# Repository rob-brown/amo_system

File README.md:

# AMO System

The Amiibo Modular Open System (AMO System) includes several components for working
with and automating amiibo on Nintendo Switch. This includes emulating a bluetooth
controller, computer vision, reading/writing amiibo files, and more. See the README
files in the respective packages in the [`apps`](apps) directory for more details about each.

# Support Us

If you want to support the development, you can [donate to the cause](https://donate.stripe.com/28ocQi4Ur9TNclW000).

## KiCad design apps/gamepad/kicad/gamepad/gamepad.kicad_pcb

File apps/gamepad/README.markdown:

# Gamepad

## Summary

The Gamepad code is able to emulate a Nintendo Switch Pro Controller. It
serves up a web interface on your local network to support loading amiibo.

## Demo

With the gamepad, you can store all your amiibo in one place. Even with large
collections of amiibo you can organize them with tags. You can pull up any of
your trained amiibo and load them into Super Smash Bros. Ultimate. With the
shuffle button, you can even load the same amiibo multiple times.

You can also use it in other games such as Tears of the Kingdom. With the
shuffle function, you can load the same amiibo repeatedly, making this the
fastest way to farm items. Note, this only works with the proxy gamepad option
since you need a joystick and L button.

Item farming is also useful in other games such as Hyrule Warriors and Skyrim.
However, Hyrule Warriors limits the number of scans per day (5). Skyrim limits
one scan per day for each amiibo ID (not serial number). You will still need to
wait or change the system clock to scan more amiibo. Other games may have similar
restrictions.

## Search

Within an amiibo collection, you can search your amiibo based on name, character,
id, and tags. Any SSBU amiibo can be search by character, ex. `character:zelda`.
You can also create any tags you want and apply them to your amiibo. You can search
tags like this: `tag:tears_of_the_kindgom`. Note that spaces in tag names must
be replaced with underscores (`_`). IDs can be searched using base16 encoding.
Partial IDs can be searched by the first bytes. For example, the full ID
`id:01070000035a0902` is not necessary. Searching `id:01070000` or `id:0107` is
often sufficient. Names can be searched without any prefix, ex. `billy`. All search
terms are case insenstive.

## Assembly

This repo includes three hardware options.

1. A simple option based on the [Adafruit Joy Bonnet](./docs/joybonnet.markdown).

2. The [AmmoBox](./docs/ammobox.markdown), a built-from-scratch option including a
custom circuit board.

3. A bring-your-own-hardware option. You plug a USB gamepad into the Pi and the
buttons and sticks are [proxied](apps/proxy_gamepad) to the Nintendo Switch via bluetooth.

Alternatively, you can make your own hardware and adjust the code accordingly.

## Initial Setup

See the common [OS Setup doc](../../docs/os-setup.markdown) for details to
install an OS for the Raspberry Pi.

## Joycontrol Installation

First, you will need to install
[Joycontrol and its dependencies](https://github.com/poohl/joycontrol).
This involves editing some system files too. You will need to manually run the
`run_controller_cli.py` script to pair your Nintendo Switch to your Raspberry Pi.

**When running joycontrol, note the MAC address if connecting to a Nintendo Switch 2**

## Gamepad Installation

You probably have `curl` and `cron` already installed. If you don't have them
installed, then you can do so like this:

```bash
sudo apt update
sudo apt install curl cron --yes
```

You can install the app for AmmoBox like this:

```bash
curl -fsSL https://raw.githubusercontent.com/rob-brown/amo_system/main/apps/gamepad/apps/hardware/install.sh | bash -s -- ammobox
```

For the Joy Bonnet:

```bash
curl -fsSL https://raw.githubusercontent.com/rob-brown/amo_system/main/apps/gamepad/apps/hardware/install.sh | bash -s -- joybonnet
```

The only difference is the platform name at the end.

If you instead want the proxy gamepad, run this for a Nintendo Switch:

```bash
curl -fsSL https://raw.githubusercontent.com/rob-brown/amo_system/main/apps/gamepad/apps/proxy_gamepad/install.sh | bash
```

If using a Nintendo Switch 2, run the following, replacing `01:23:45:67:89:AB` with the
MAC address you found when manually running Joycontrol earlier.

```bash
curl -fsSL https://raw.githubusercontent.com/rob-brown/amo_system/main/apps/gamepad/apps/proxy_gamepad/install.sh | bash -s -- 01:23:45:67:89:AB
```

> **WARNING:** You shouldn't just trust someone to run an arbitrary script on your
system, especially one that has root permissions like this one does. Take some
time and look over the script to ensure it's not doing anything nefarious. You
can also run the commands yourself to better see the effects.

Once you've installed the app, you will need to pair your Pi with your Nintendo
Switch. Then every time after your Pi boots, it will try to connect to your
Nintendo Switch.

## Web Interface

See the [web interface doc](./docs/web-interface.markdown) for details on how to use
the web interface to load and use amiibo.

## Troubleshooting

If you are having trouble with the web interface, make sure your cron file (ex. `/etc/cron.d/proxy`) is using the same
host name as your Pi. You can find the host name by running `hostname` from the console. If your host name is `raspberrypi`,
then make sure your cron file has `PHX_HOST=raspberrypi.local`.

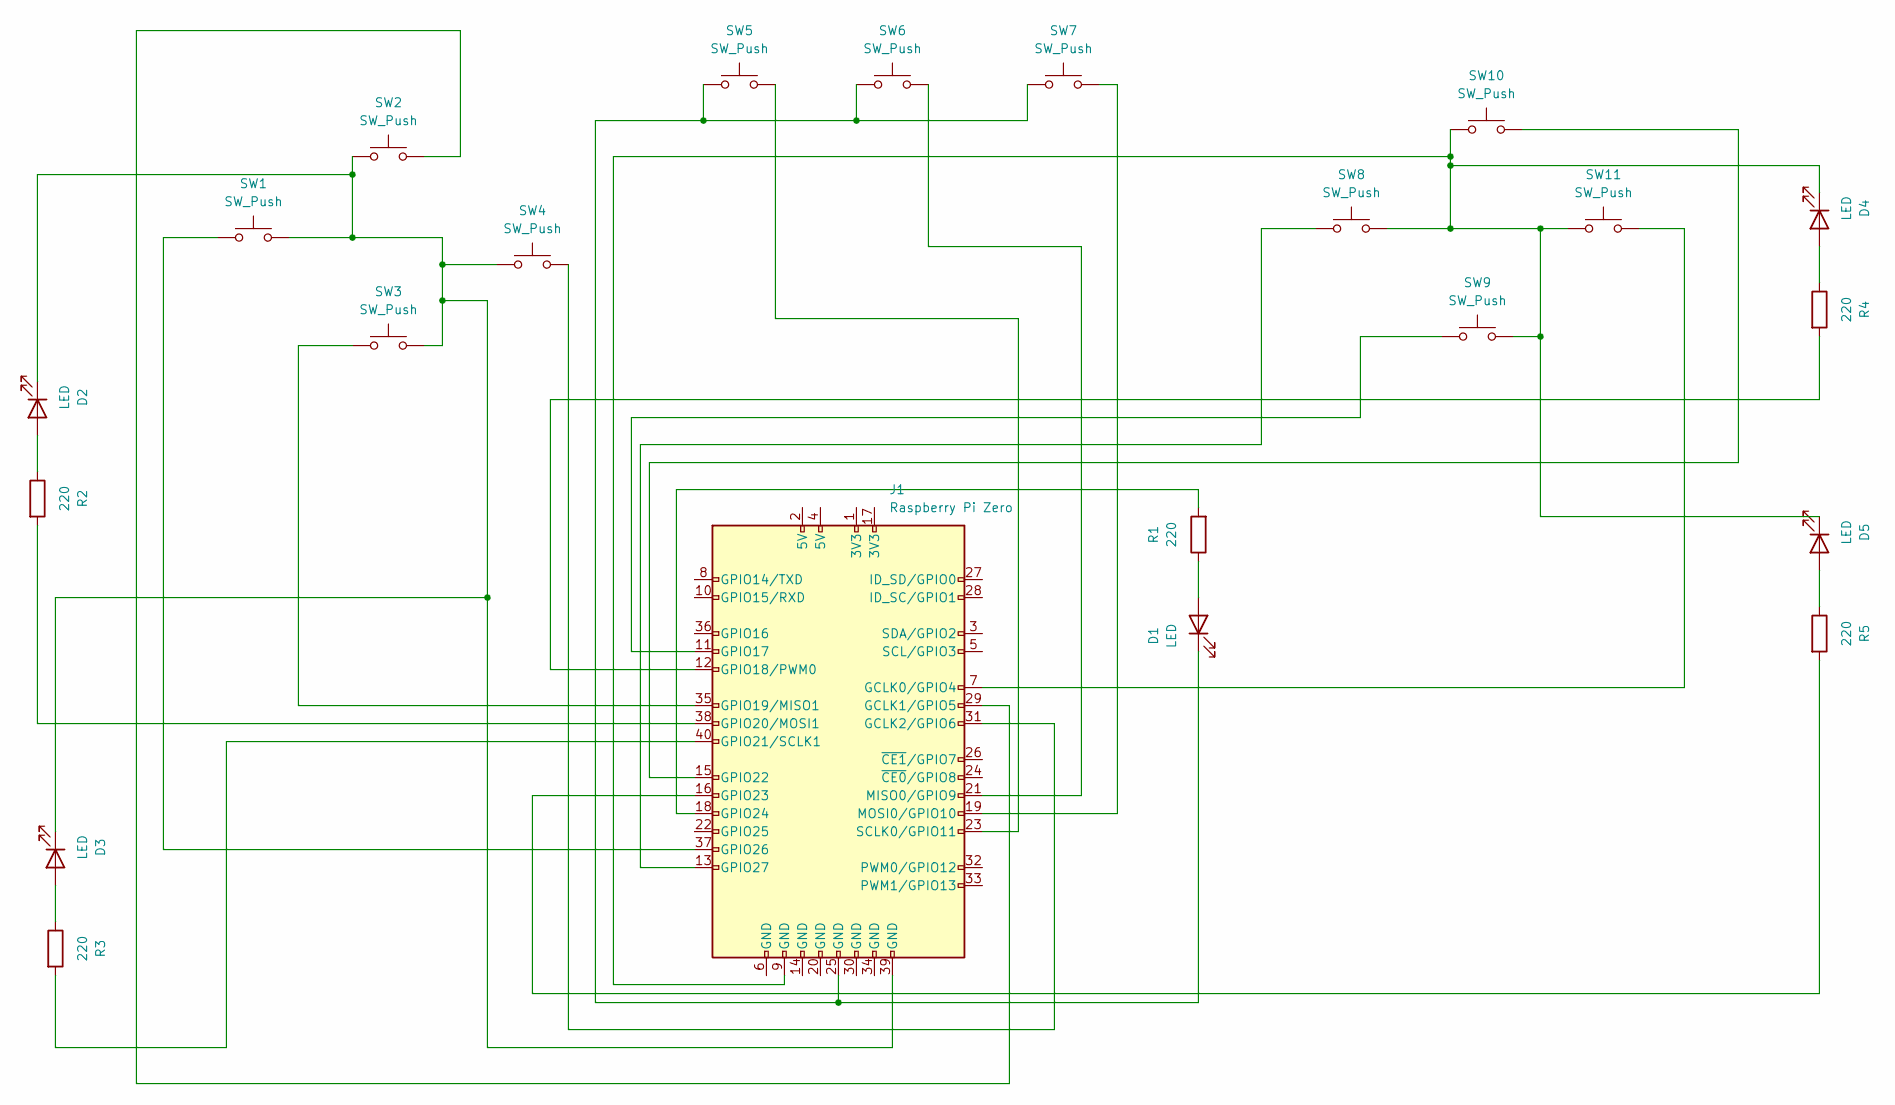
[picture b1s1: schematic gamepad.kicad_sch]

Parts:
D1: LED; LED_D3.0mm_Horizontal_O1.27mm_Z2.0mm
D2, D3, D4, D5: LED; LED_D5.0mm
J1: Raspberry Pi Zero; PinHeader_2x20_P2.54mm_Vertical
R1, R2, R3, R4, R5: 220; R_Axial_DIN0204_L3.6mm_D1.6mm_P7.62mm_Horizontal
SW1, SW2, SW3, SW4, SW5, SW6, SW7, SW8, SW9, SW10, SW11: SW_Push; SW_PUSH_6mm_H5mm

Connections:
unnamed: D1.1 (K), J1.25 (GND), SW5.1, SW6.1, SW7.1
unnamed: D1.2 (A), R1.1
unnamed: D2.2 (A), R2.1
unnamed: D3.2 (A), R3.1
unnamed: D4.2 (A), R4.1
unnamed: D5.2 (A), R5.1
unnamed: J1.7 (GCLK0/GPIO4), SW11.2
unnamed: D4.1 (K), D5.1 (K), J1.9 (GND), SW8.2, SW9.2, SW10.1, SW11.1
unnamed: J1.11 (GPIO17), SW9.1
unnamed: J1.12 (GPIO18/PWM0), R4.2
unnamed: J1.13 (GPIO27), SW8.1
unnamed: J1.15 (GPIO22), SW10.2
unnamed: J1.16 (GPIO23), R5.2
unnamed: J1.18 (GPIO24), R1.2
unnamed: J1.19 (MOSI0/GPIO10), SW7.2
unnamed: J1.21 (MISO0/GPIO9), SW6.2
unnamed: J1.23 (SCLK0/GPIO11), SW5.2
unnamed: J1.29 (GCLK1/GPIO5), SW2.2
unnamed: J1.31 (GCLK2/GPIO6), SW4.2
unnamed: J1.35 (GPIO19/MISO1), SW3.1
unnamed: J1.37 (GPIO26), SW1.1
unnamed: J1.38 (GPIO20/MOSI1), R2.2
unnamed: D2.1 (K), D3.1 (K), J1.39 (GND), SW1.2, SW2.1, SW3.2, SW4.1
unnamed: J1.40 (GPIO21/SCLK1), R3.2

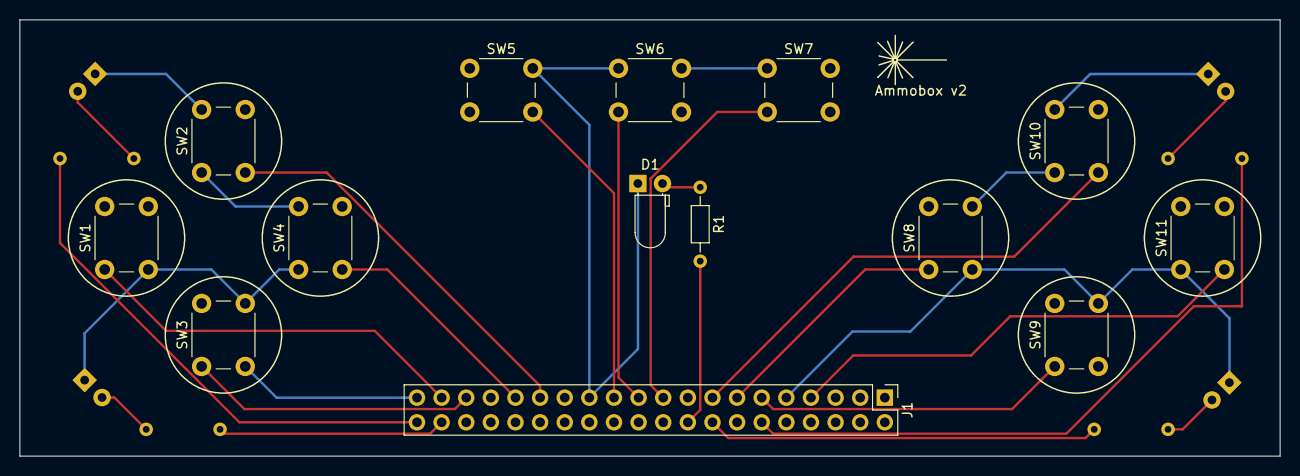
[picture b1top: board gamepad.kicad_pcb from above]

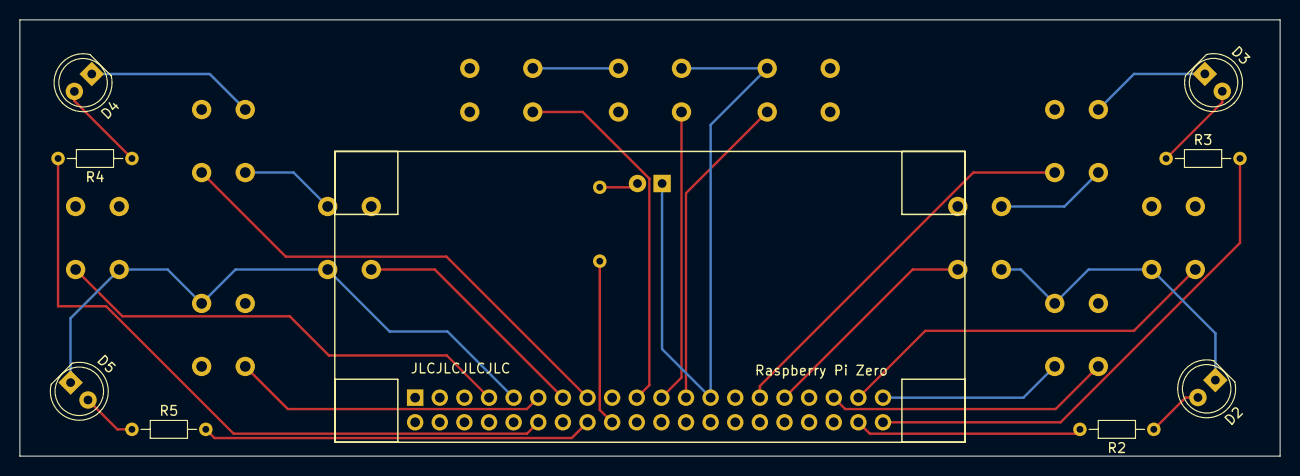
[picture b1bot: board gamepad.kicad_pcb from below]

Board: 2 copper layers, 130.0 x 45.0 mm, 22 parts (8 on the bottom side), 24 nets.

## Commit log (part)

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2023-01-14 Add joycontrol
2023-01-14 Add amiibo_serialization
2023-01-14 Add amiibo_automation
2023-01-14 Add vision
2023-01-15 Rename amiibo_automation to autopilot
2023-01-15 Allow units in durations
2023-01-15 Remove old scripting
2023-01-15 Add start_link functions
2023-01-15 Fix app name
2023-01-15 Fix some paths
2023-01-15 Use luerl directly
2023-01-15 Fix function signatures
2023-01-15 Fix new press command
2023-01-15 Add defaults
2023-01-15 Add more functionality to Lua scripts
2023-01-15 Fix bindings
2023-01-15 Fix functions that return results
2023-01-15 Fix pointer call
2023-01-15 Fix pointer coordinates
2023-01-15 Document some functions
2023-01-15 Document some more scripting details
2023-01-16 Make file paths relative to the script file
2023-01-16 Fix some Lua functions
2023-01-16 Write up README files
2023-01-16 Add more README details
2023-01-16 Another README update
2023-01-16 Add Challonge library
2023-01-17 Add tournament runner
2023-01-17 Add some missing details
2023-01-17 Fix squad strike script
2023-01-17 Improve squad strike error detection
2023-01-21 Add submission_info
2023-01-22 Start standardizing automation scripts
2023-01-22 Fix errors in new automation
2023-01-22 Clean up old code
2023-01-22 Add a 1v1 automation driver
2023-01-22 Fix 1v1 scripts
2023-02-19 Add a to do for 1v1
2023-02-19 mix format
2023-02-20 Start adding gamepad
2023-02-21 Fix some of the gamepad bugs
2023-02-22 Track button states
2023-02-22 Fix minor issues with joystick
2023-02-22 Fix scripts
2023-02-22 Fix loading amiibo
2023-02-23 Add a release builder for tournament_runner
2023-03-02 Start adding Gamepad documentation
2023-03-12 Add support for AmmoBox and JoyBonnet
2023-03-12 Fix bugs with startup
2023-04-15 Update BoM docs
2023-04-16 Add install script
2023-04-16 Improve install script with output
2023-04-16 Start adding gamepad docs
2023-04-16 Fix BoM cost
2023-04-16 Add some README files for GitHub
2023-04-16 Migrate database on install
2023-04-16 Fix install script
2023-04-16 Reorder install script
2023-04-16 Fix startup script
2023-04-16 Set user for startup script
2023-04-16 Update page title
2023-04-29 Add SSBU amiibo data extraction
2023-04-29 Better handle decryption keys
2023-04-29 Fix typo
2023-04-29 Fix another typo
2023-04-29 Remove comment to make the file import friendly
2023-04-30 Add a Livebook showing personality calculation
2023-04-30 Clean up some of the personality Livebook
2023-05-02 Add tournament runner instructions
2023-05-02 Add note about supported capture cards
2023-05-02 Add notes to the Tournament Runner Livebook
2023-05-03 Add Livebook for creating heat maps from bins
2023-05-03 Add a title to heat maps
2023-05-04 Reorganize heat map Livebook
2023-05-04 Make focusing on a bin easier
2023-05-26 Create a safe serial number when shuffling
2023-05-26 Add missing case
2023-05-26 Minor text changes
2023-05-26 Add another detail
2023-06-03 Remove AmiiboSN-Changer check
2023-06-04 Include the focused bin’s personality.
    Also, re-evaluate the Livebook when the inputs change.
2023-06-04 Allow focusing on two bins
2023-06-09 Evaluate cells automatically
2023-07-07 Update paths for releases
2023-07-07 Add notes to install OpenCV
2023-07-07 Modify install script to start iex for convenience
2023-08-18 Start new Rabbit Driver tool
2023-08-18 Fix screenshots
2023-08-20 Allow running giving scripts
2023-08-20 Add a Livebook
2023-08-20 Allow running scripts without first sending the file
2023-08-22 Use Data URLs for sending binary data
2023-08-23 Add image visible call
2023-08-23 Add image.visible message
2023-08-23 Change vision.screenshot to image.screenshot
2023-08-25 Send logs to RabbitMQ
2023-08-25 Update Livebook for logs
2023-08-25 Remove log hack
2023-08-28 Use the target to disable RPi dependencies
2023-08-28 Handle improper lists
2023-08-28 Protect file system better
2023-08-28 Start porting Squad Strike
2023-08-28 Fix compiler errors
2023-08-28 Change configuration to work with Livebook
2023-08-28 Start updating Livebook with helper project
2023-08-28 Update the rest of the Livebook
2023-08-28 Fix image references in scripts
2023-09-02 Fix some automation problems
2023-09-02 Run scripts through command queue
2023-09-02 Revert command queue change
2023-09-02 Add debug mode to the Lua scripts
2023-09-02 Fix issues with timeout
2023-09-02 Get Rabbit Driver ready for release
2023-09-02 Add env var to build script
2023-09-02 Change how supervision tree is set up
2023-09-02 Try setting the target at run time
2023-09-02 Fix target setting
2023-09-02 Update docs
2023-09-02 Fix fragment
2023-09-02 Fix JSON examples
2023-09-02 Remove unimplemented messages
2023-09-04 Add installation and FAQ
2023-09-04 Add missing character
2023-09-04 Fix other HTML issues
2023-09-04 Format FAQ
2023-09-04 Format README some more
2023-09-04 Revert blockquote change
2023-09-04 Add link to Livebook
2023-09-06 Fix a couple comments
2023-09-06 Start porting to evision
2023-09-06 Implement more vision functions
2023-09-08 Finish porting OpenCV functions
2023-09-08 Point Rabbit Driver to new Vision code
2023-09-08 Update Squad Strike runner for new Vision code
2024-02-16 Add Sora
2024-02-24 Update for Sora
2024-02-27 Fix rabbit_driver install script
2024-03-01 Add “best of n” to tournament_runner
2024-03-01 Include better error message on fail
2024-03-01 Use new Vision code
2024-03-01 Fix return types
2024-03-01 Fix timeout duration
2024-03-01 Improve cropping
2024-03-02 Fix Logger.warn
2024-03-02 Crop relative to image
2024-03-02 Crop closer to determine score
2024-03-02 Fix score detection
2024-03-02 Another score detection fix
2024-03-02 Fix winner detection
2024-03-02 Fix max score
2024-03-02 Actually fix winner’s score
2024-03-02 Add sanity check to ensure loser doesn’t win
2024-03-02 Improve chance of getting the right score
2024-03-02 Wait between score reads
2024-03-02 Fix run order
2024-03-02 Debug score capture
2024-03-02 Debug cropped image
2024-03-02 Replace best of n image
2024-03-02 Require higher confidence level
2024-03-02 Use different heuristic for bo3
2024-03-03 Only clear amiibo cache when amiibo seen twice
2024-03-03 Handle missing costumes
2024-03-03 Fix order of clearing amiibo cache
2024-03-03 Fix cache-clearing logic
2024-03-03 Actually clear the tracker
2024-03-07 Use USAC standard bracket names
2024-03-09 Starting gamepad proxy
2024-03-10 Add in response parsing
2024-03-10 Fix tests and warnings
2024-03-10 Get running on Pi
2024-03-10 Process controller events
2024-03-10 Fix controller mappings
2024-03-10 Fix XBOX mapping
2024-03-10 Map right joystick to dpad too
2024-03-14 Start adding UI for proxy gamepad
2024-03-15 Add web interface to connect gamepad
2024-03-16 Properly handle joysticks
2024-03-16 Add more controller mappings
2024-03-16 Add shuffle serial button
2024-03-18 Hide vc4 devices
2024-03-21 Allow non-SSBU amiibo
2024-03-22 Add axis configuration
2024-03-22 Update docs for proxy gamepad
2024-03-22 Encode amiibo IDs for searching
2024-03-22 Use base 16 instead of 64
2024-03-22 Tag builds with bit size
2024-03-22 Add demo videos to README
2024-03-22 Embed the videos differently
2024-03-30 Handle errors and fix install
2024-04-09 Remove unnecessary sudo
2024-04-09 Add troubleshooting to README
2024-06-07 Replace deprecated library
2024-06-07 Fix key_retail config
2024-06-08 Restart Joycontrol if the writer stops
2025-02-15 Add new library TrueSkill
2025-02-15 Update TrueSkill README
2025-02-16 Add character names
2025-02-16 Fix warnings
2025-02-18 Fix type error
2025-05-02 Fix bug in Joycontrol code
    Ignore missing event loop on start up. Fixes repeated ‘Writer exited…’ error.
2025-06-11 Fix proxy_gamepad for Nintendo Switch 2
2026-01-03 [SSBU] Append (WoL) to skill tree abilities
2026-01-18 Add picopad and new Squad Strike Livebook
2026-01-19 Avoid going to photos app
2026-01-19 Remove inspect
2026-02-12 Add picopad firmware
2026-02-13 Add new gamepad proxy designed for picopad
2026-02-13 Fix some UI issues with amiibo
2026-02-13 Improve button mapping
2026-02-13 Document the tested controllers
2026-02-13 Remove unnecessary axes mappings
2026-02-13 Fix status parse issue
2026-02-13 Automatically (re-)connect to picopad
2026-02-14 Rename AGENTS.md -> CLAUDE.md
2026-02-14 Slim down dependencies
2026-02-18 [Picopad] Add read_amiibo command
2026-04-02 [Bracket] Initial commit
2026-04-02 [Bracket] Phase 2
2026-04-03 Add image support
2026-04-04 Improve formatting
2026-04-05 Fix losers bracket
